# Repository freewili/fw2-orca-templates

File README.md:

# fw2-orca-templates

Example project templates for the FreeWili 2 ORCA module.

Currently supports:

- [KiCad](./kicad) — schematic/PCB template (`ORCATemplate`)
- [Connector pinouts](./PINOUTS.md) — Free Wili OG and Free Wili 2 20-position and 10-position connector pin tables
- [ORCA_NRF example](./examples/ORCA_NRF) — example ORCA module board carrying an NRF24L01 radio
- [GPIO Joiner example](./examples/gpiojoiner) — a routed KiCad 10 star board for testing a pair of FreeWili 2 / OG devices, with fabrication and assembly files

## KiCad template

The `kicad/` directory contains a starter KiCad 7 project (`ORCATemplate`) for
building ORCA module boards, including a 3D `.step` model and a custom
`EEPROM.pretty` footprint library.

The ORCA module connects via two headers, `CN1` and `CN2`:

> **Note:** `kicad/fp-lib-table` currently references footprint libraries
> (`IDC_10`, `IDC_20`) by absolute path on another machine. Update these
> library paths (or replace them with the project-relative `${KIPRJMOD}`
> style used for `EEPROM`) before relying on the template on a fresh
> checkout.

## ORCA_NRF example

The `examples/ORCA_NRF/` directory contains a complete example ORCA module
project built from the template: an NRF24L01 radio carrier with the `CN1`
(20-pin) and `CN2` (10-pin) headers and the ID EEPROM.

User-provided photograph of the assembled ORCA NRF board.

> **Note:** The symbols and footprints are embedded in the schematic and PCB,
> so the project opens without extra libraries. The 3D model references in
> `ORCA_NRF.kicad_pcb` use absolute paths from another machine and will show
> as missing in the 3D viewer until you repoint them.

## GPIO Joiner example

[GPIO Joiner rev A](./examples/gpiojoiner) provides two opposing FreeWili 2
positions and two opposing OG positions. Connect one device per electrical
side, two devices total. A 24LC02BT ORCA EEPROM connects to shared FW2 I2C1.

The example includes editable KiCad sources, project-local symbols,
footprints and 3D models, top/bottom board images, a schematic PDF, and
[prototype manufacturing files](./examples/gpiojoiner/hardware/gpiojoiner/manufacturing/revA).
The [PCBWay quote-form answers](./examples/gpiojoiner/hardware/gpiojoiner/manufacturing/PCBWAY-QUOTE-ANSWERS.md)
show how to request five fully assembled prototypes.

This is an unbuilt prototype: physical mating, EEPROM ID programming and
bench operation remain to be validated. Optional R5-R8 models appear in the
preview but are DNP in the assembly BOM. See the example README for operating
limits and verification evidence.

Repository agent workflow is documented in [AGENTS.md](./AGENTS.md).

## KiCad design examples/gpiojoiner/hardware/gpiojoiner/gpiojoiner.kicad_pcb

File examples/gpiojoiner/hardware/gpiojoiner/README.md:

# GPIO Joiner - rev A review prototype

Open **gpiojoiner.kicad_pro** in KiCad 10 or newer. The schematic, PCB,
symbol library, footprints, and 3D models are included in this folder.
See [schematic PDF](previews/schematic.pdf), [board preview](previews/pcb-top.png),
[design details](DESIGN.md), and [BOM](BOM.md).

[Prototype manufacturing package and order settings](manufacturing/revA/README.md)
are prepared for JLCPCB and PCBWay, including Gerbers, exact-part BOMs,
supplier placement CSVs, and a 1:1 fit/assembly PDF. The working quantity is
five fully assembled boards. No supplier order or live quote has been submitted.

| Top view | Bottom view |
| --- | --- |
|  |  |

These are CAD previews; full device enclosures and physical mating are not
verified. Optional R5-R8 models appear in the views but are DNP in the
prototype assembly BOM.

This revision implements the test cable described in the root
`gpiojoiner spec.md`. It has four docking positions in a star, intended
for **two attached devices: one on Side A and one on Side B**.

```text
                         OG A - J5
                            |
 FW2 A - J1 + J2 -------- JOINER -------- J3 + J4 - FW2 B
                            |
                         OG B - J6
```

| Test pair | Side A | Side B | SW1 position |
| --- | --- | --- | --- |
| FW2 / FW2 | West: J1 and J2 | East: J3 and J4 | FW2 / MIXED |
| OG / OG | North: J5 | South: J6 | OG / OG |
| FW2 / OG | West: J1 and J2 | South: J6 | FW2 / MIXED |
| OG / FW2 | North: J5 | East: J3 and J4 | FW2 / MIXED |

The two connector choices on a side share signals. Four simultaneously
attached devices, or two attached to the same side, are unsupported.
Supporting four attached devices would require added switching or isolation.

## Setup and tests

1. With both devices off, connect one device per side and set SW1.
2. In FW2 / MIXED mode, configure exactly one FW2 to supply VREF; the other
   device uses that external reference. In OG / OG mode, SW1 connects each
   OG's VREF to its own 3.3 V output. Change the switch with power off.
3. Power both devices before driving the shared interfaces. Configure GPIO
   directions and use one SPI clock/chip-select driver. UART/SPI data,
   UART flow control, and GPIO26/27 are crossed as specified.
4. For FW2 / FW2 analog tests, read AOUT0/1 on the other device's AIN0/1.
   Read programmable VOUT as **2 x the opposite AIN2 reading**. Two 10k/10k
   dividers accommodate the published 5.5 V programmable-output maximum.
   AIN3 and GPIO25 have labeled test pads only.

CAN connects only the two FW2 ports; OG SWD pins are unconnected. R7/R8 CAN
termination and R5/R6 I2C1 pull-ups are **DNP**. Check the devices' existing
termination and pull-ups before populating these optional resistors.

## ORCA identification

One **24LC02BT-E/OT** is permanently connected to the shared I2C1 bus on
both FW2 10-pin connectors (pin 7 SCL, pin 9 SDA). Its WP pin is grounded
for programming. A BAT54C diode OR powers it from either FW2's 3.3 V output
without directly joining those supply outputs.

Use a 3.3 V I2C1 bus, up to 400 kHz, with verified pull-ups. I2C1 voltage is
independent of the selected GPIO VREF. Reserve addresses **0x50 through
0x57**: this EEPROM ignores the three low address bits. Coordinate the two
hosts so only one controller accesses the bus at a time unless their
multi-controller behavior has been verified. The diode OR does not isolate
shared signal pins from an unpowered host.

The EEPROM hardware is included; a product-specific ORCA identification
image and a verified programming/boot procedure are still needed. No
identification contents or working auto-detection are claimed by this project.

## Physical and bench validation

The PCB is a 130 x 130 mm cross, two layers, 1.6 mm thick, with four 3.2 mm
mounting holes. FW2 20/10 connector centers are 26.72 mm apart, matching the
named starter template. The original example differs by 0.03 mm. Connector
centers are 3 mm inside the mating board edges. The included connector
models come from the template assembly; full device enclosures were not
available for clearance verification.

Before ordering the prototype, verify actual mating orientation, connector
gender/keying, spacing, board-to-case clearance, and support with real FW2
and OG devices. Check both SW1 contact states on the purchased part. The
project-local switch footprint corrects the installed library's reversed
second-row numbering using the manufacturer contact diagram.

Bench validation must also cover EEPROM supply voltage/read/write and
identification, both VREF modes, power sequencing, I2C pull-ups/ownership,
CAN termination, analog input loading/settling and divider calibration,
and the required test firmware for all four permitted pairs. Manufacturing
inputs are available for prototype quotation and engineering review; hardware
operation remains unverified and this is not a production release.

## Rechecking or regenerating

The editable KiCad files are the delivered design. For a full recheck,
run `tools/verify_project.py` with KiCad's bundled Python; it refreshes the
netlist, ERC/DRC, audits, and verification report. Alternatively, run the standard Python
`tools/check_connections.py` against a freshly exported KiCad XML netlist,
and run `tools/check_pcb.py` with KiCad's bundled Python (`pcbnew`). Also
run KiCad ERC and DRC with schematic parity enabled. Final reports belong
in `reports/`.

`generate_schematic.py` and `generate_pcb.py --rebuild` recreate the CAD
sources and **overwrite manual edits**. The PCB generator requires the
referenced template checkout and installed KiCad libraries. Rebuilding
removes routing. `route_pcb.py --java <java25> --jar <freerouting.jar>`
routes a board with no existing tracks and fills its ground pours.
`finish_routing.py` applies the local edge/thermal and label edits for the
delivered rev A routing; it is specific to those coordinates. A new router
run can produce different geometry and needs a fresh review and finishing
edits. Final KiCad DRC remains required. These development tools are optional for
opening and editing the delivered project.

Library origins and the source revision are recorded in [PROVENANCE.md](PROVENANCE.md).

Optional regeneration tools default to the Windows KiCad 10 install path.
Set `KICAD_INSTALL` for a different installation, and `KICAD_SYMBOL_DIR` when
the symbols are in a separate location. Verification accepts `--cli` for
the KiCad CLI path and needs Python with `pcbnew`. Opening the delivered
project does not require these development scripts or a template checkout.

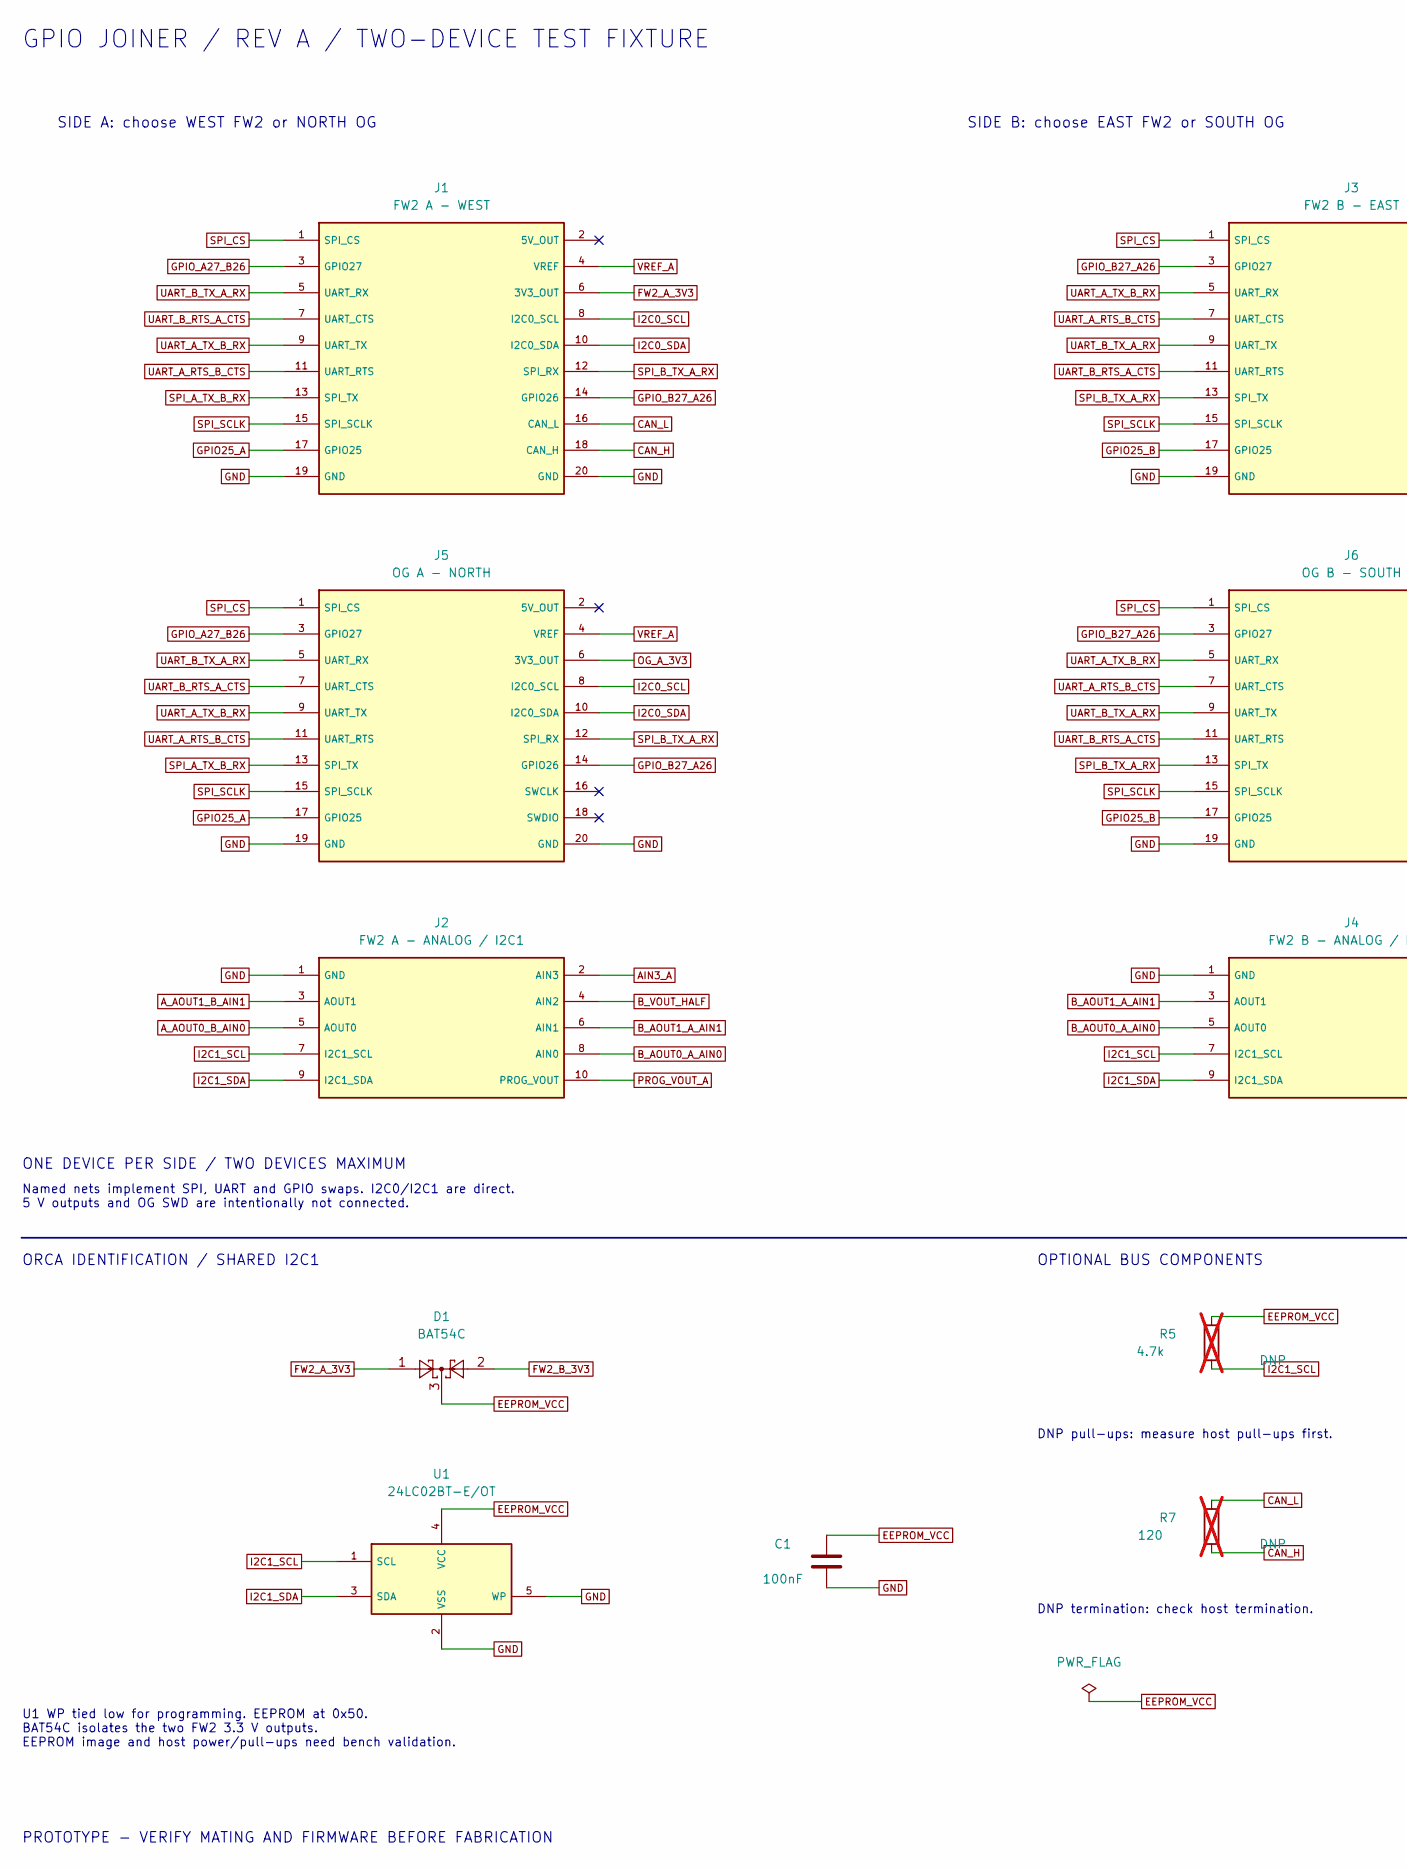
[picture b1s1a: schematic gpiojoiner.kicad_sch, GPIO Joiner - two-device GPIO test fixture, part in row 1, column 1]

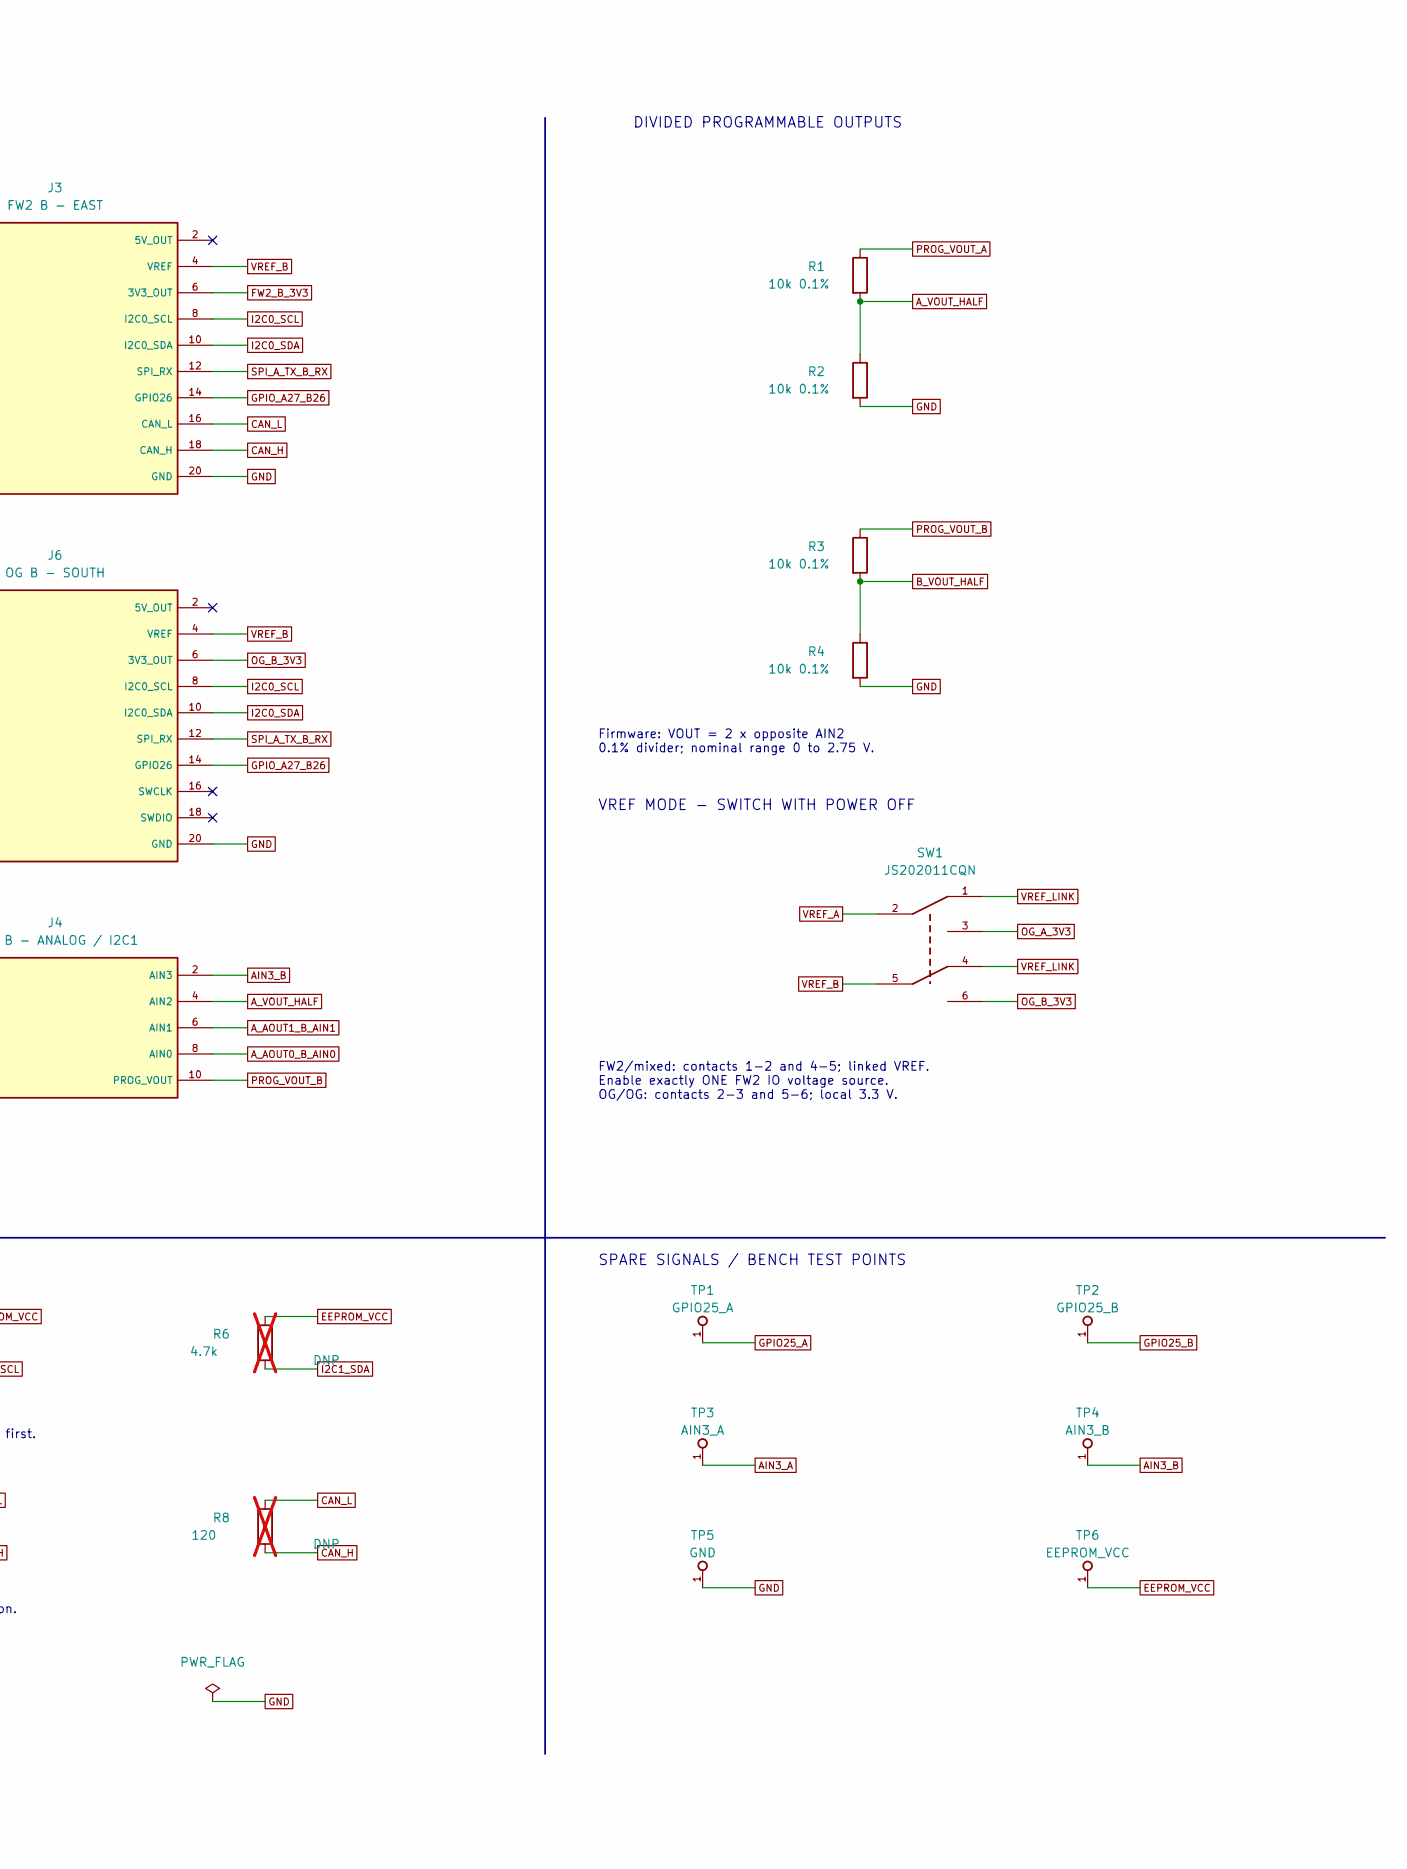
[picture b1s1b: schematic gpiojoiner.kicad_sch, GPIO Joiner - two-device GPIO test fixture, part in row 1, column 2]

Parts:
C1: 100nF; C_0603_1608Metric
D1: BAT54C; SOT-23
J1: FW2 A - WEST; ORCA_20_RA
J2: FW2 A - ANALOG / I2C1; ORCA_10_RA
J3: FW2 B - EAST; ORCA_20_RA
J4: FW2 B - ANALOG / I2C1; ORCA_10_RA
J5: OG A - NORTH; ORCA_20_RA
J6: OG B - SOUTH; ORCA_20_RA
R1, R2, R3, R4: 10k 0.1%; R_0603_1608Metric
R5, R6: 4.7k; R_0603_1608Metric; not fitted
R7, R8: 120; R_0603_1608Metric; not fitted
SW1: JS202011CQN; SW_JS202011CQN
TP1: GPIO25_A; TestPoint_Pad_D1.5mm
TP2: GPIO25_B; TestPoint_Pad_D1.5mm
TP3: AIN3_A; TestPoint_Pad_D1.5mm
TP4: AIN3_B; TestPoint_Pad_D1.5mm
TP5: GND; TestPoint_Pad_D1.5mm
TP6: EEPROM_VCC; TestPoint_Pad_D1.5mm
U1: 24LC02BT-E/OT; SOT-23-5

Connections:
AIN3_A: J2.2 (AIN3), TP3.1
AIN3_B: J4.2 (AIN3), TP4.1
A_AOUT0_B_AIN0: J2.5 (AOUT0), J4.8 (AIN0)
A_AOUT1_B_AIN1: J2.3 (AOUT1), J4.6 (AIN1)
A_VOUT_HALF: J4.4 (AIN2), R1.2, R2.1
B_AOUT0_A_AIN0: J2.8 (AIN0), J4.5 (AOUT0)
B_AOUT1_A_AIN1: J2.6 (AIN1), J4.3 (AOUT1)
B_VOUT_HALF: J2.4 (AIN2), R3.2, R4.1
CAN_H: J1.18 (CAN_H), J3.18 (CAN_H), R7.2, R8.2
CAN_L: J1.16 (CAN_L), J3.16 (CAN_L), R7.1, R8.1
EEPROM_VCC: C1.1, D1.3, R5.1, R6.1, TP6.1, U1.4 (VCC)
FW2_A_3V3: D1.1, J1.6 (3V3_OUT)
FW2_B_3V3: D1.2, J3.6 (3V3_OUT)
GND: C1.2, J1.19 (GND), J1.20 (GND), J2.1 (GND), J3.19 (GND), J3.20 (GND), J4.1 (GND), J5.19 (GND), J5.20 (GND), J6.19 (GND), J6.20 (GND), R2.2, R4.2, TP5.1, U1.2 (VSS), U1.5 (WP)
GPIO25_A: J1.17 (GPIO25), J5.17 (GPIO25), TP1.1
GPIO25_B: J3.17 (GPIO25), J6.17 (GPIO25), TP2.1
GPIO_A27_B26: J1.3 (GPIO27), J3.14 (GPIO26), J5.3 (GPIO27), J6.14 (GPIO26)
GPIO_B27_A26: J1.14 (GPIO26), J3.3 (GPIO27), J5.14 (GPIO26), J6.3 (GPIO27)
I2C0_SCL: J1.8 (I2C0_SCL), J3.8 (I2C0_SCL), J5.8 (I2C0_SCL), J6.8 (I2C0_SCL)
I2C0_SDA: J1.10 (I2C0_SDA), J3.10 (I2C0_SDA), J5.10 (I2C0_SDA), J6.10 (I2C0_SDA)
I2C1_SCL: J2.7 (I2C1_SCL), J4.7 (I2C1_SCL), R5.2, U1.1 (SCL)
I2C1_SDA: J2.9 (I2C1_SDA), J4.9 (I2C1_SDA), R6.2, U1.3 (SDA)
OG_A_3V3: J5.6 (3V3_OUT), SW1.3
OG_B_3V3: J6.6 (3V3_OUT), SW1.6
PROG_VOUT_A: J2.10 (PROG_VOUT), R1.1
PROG_VOUT_B: J4.10 (PROG_VOUT), R3.1
SPI_A_TX_B_RX: J1.13 (SPI_TX), J3.12 (SPI_RX), J5.13 (SPI_TX), J6.12 (SPI_RX)
SPI_B_TX_A_RX: J1.12 (SPI_RX), J3.13 (SPI_TX), J5.12 (SPI_RX), J6.13 (SPI_TX)
SPI_CS: J1.1 (SPI_CS), J3.1 (SPI_CS), J5.1 (SPI_CS), J6.1 (SPI_CS)
SPI_SCLK: J1.15 (SPI_SCLK), J3.15 (SPI_SCLK), J5.15 (SPI_SCLK), J6.15 (SPI_SCLK)
UART_A_RTS_B_CTS: J1.11 (UART_RTS), J3.7 (UART_CTS), J5.11 (UART_RTS), J6.7 (UART_CTS)
UART_A_TX_B_RX: J1.9 (UART_TX), J3.5 (UART_RX), J5.9 (UART_TX), J6.5 (UART_RX)
UART_B_RTS_A_CTS: J1.7 (UART_CTS), J3.11 (UART_RTS), J5.7 (UART_CTS), J6.11 (UART_RTS)
UART_B_TX_A_RX: J1.5 (UART_RX), J3.9 (UART_TX), J5.5 (UART_RX), J6.9 (UART_TX)
VREF_A: J1.4 (VREF), J5.4 (VREF), SW1.2
VREF_B: J3.4 (VREF), J6.4 (VREF), SW1.5
VREF_LINK: SW1.1, SW1.4

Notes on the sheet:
GPIO JOINER / REV A / TWO-DEVICE TEST FIXTURE
SIDE A: choose WEST FW2 or NORTH OG
SIDE B: choose EAST FW2 or SOUTH OG
DIVIDED PROGRAMMABLE OUTPUTS
Firmware: VOUT = 2 x opposite AIN2 0.1% divider; nominal range 0 to 2.75 V.
ONE DEVICE PER SIDE / TWO DEVICES MAXIMUM
Named nets implement SPI, UART and GPIO swaps. I2C0/I2C1 are direct. 5 V outputs and OG SWD are intentionally not connected.
ORCA IDENTIFICATION / SHARED I2C1
OPTIONAL BUS COMPONENTS
DNP pull-ups: measure host pull-ups first.
DNP termination: check host termination.
VREF MODE - SWITCH WITH POWER OFF
FW2/mixed: contacts 1-2 and 4-5; linked VREF. Enable exactly ONE FW2 IO voltage source. OG/OG: contacts 2-3 and 5-6; local 3.3 V.
SPARE SIGNALS / BENCH TEST POINTS
U1 WP tied low for programming. EEPROM at 0x50. BAT54C isolates the two FW2 3.3 V outputs. EEPROM image and host power/pull-ups need bench validation.
PROTOTYPE - VERIFY MATING AND FIRMWARE BEFORE FABRICATION

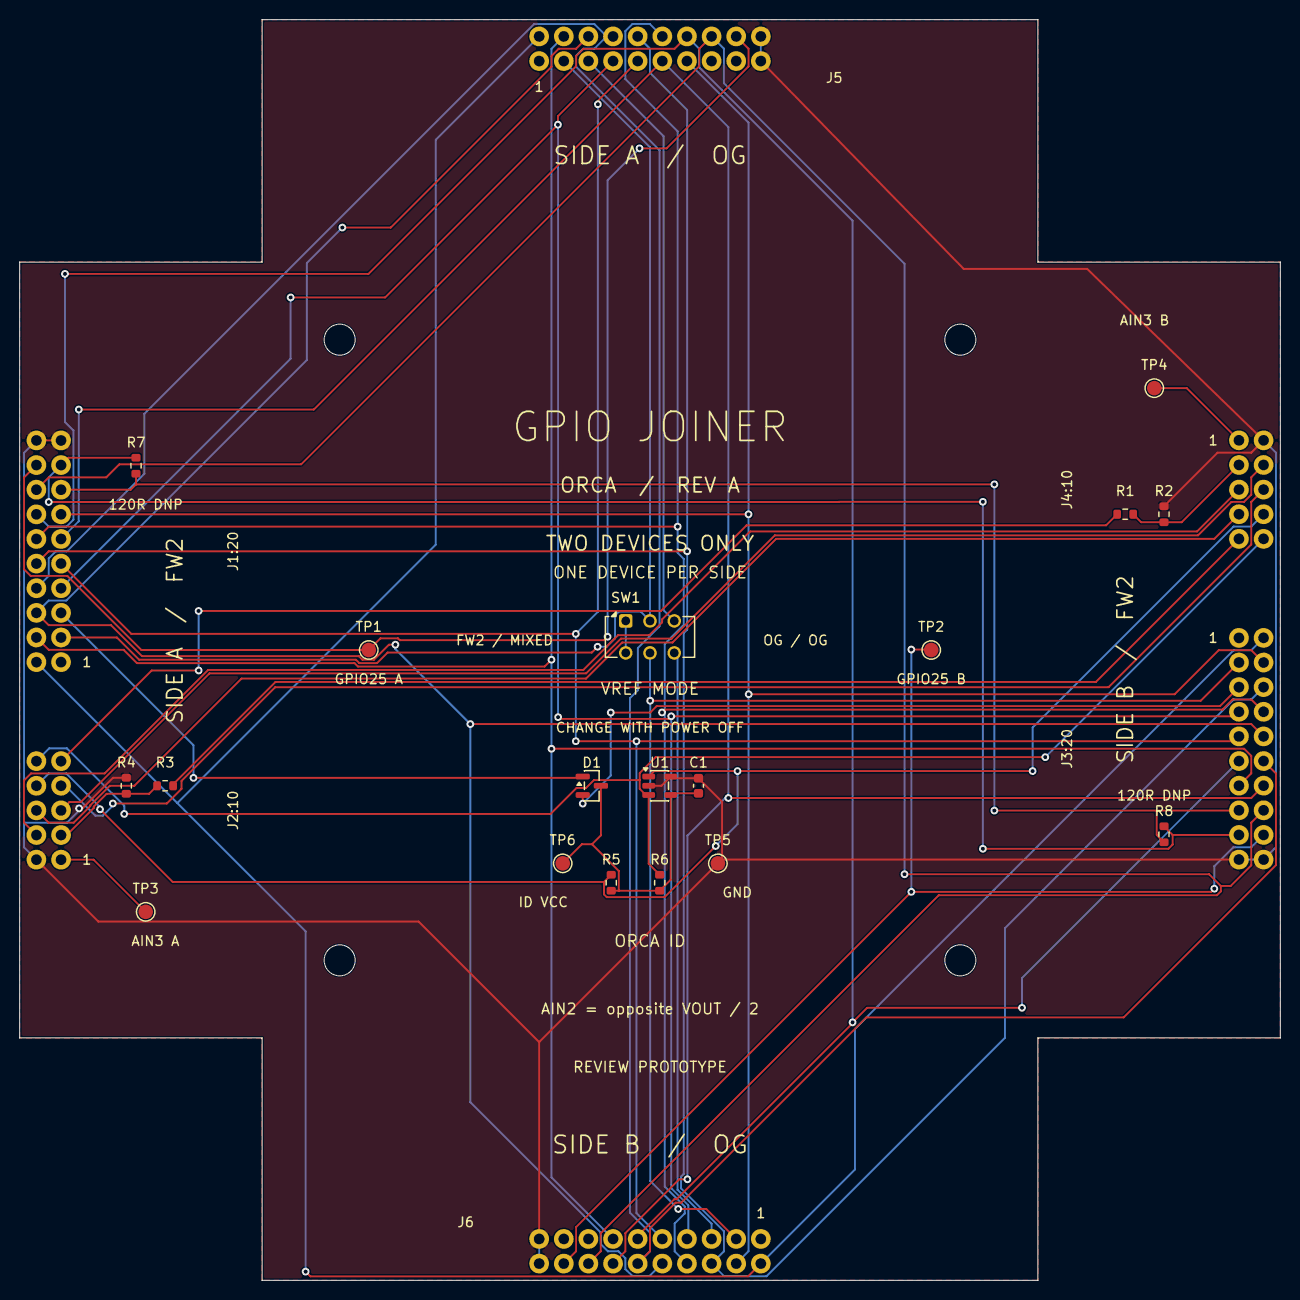
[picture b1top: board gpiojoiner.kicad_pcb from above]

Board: 2 copper layers, 130.0 x 130.0 mm, 28 parts (0 on the bottom side), 37 nets.

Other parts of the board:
H1, H2, H3, H4: MountingHole_3.2mm_M3

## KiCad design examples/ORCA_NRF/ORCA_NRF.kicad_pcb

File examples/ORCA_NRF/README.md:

# ORCA NRF example

NRF radio carrier example for FreeWili 2.

Open [ORCA_NRF.kicad_pro](ORCA_NRF.kicad_pro) in KiCad to inspect the
[schematic](ORCA_NRF.kicad_sch) and [PCB](ORCA_NRF.kicad_pcb).

The photograph shows the assembled example board. The existing PCB's 3D
model references include absolute paths; see the [repository notes](../../README.md#orca_nrf-example)
when opening its 3D view on another machine.

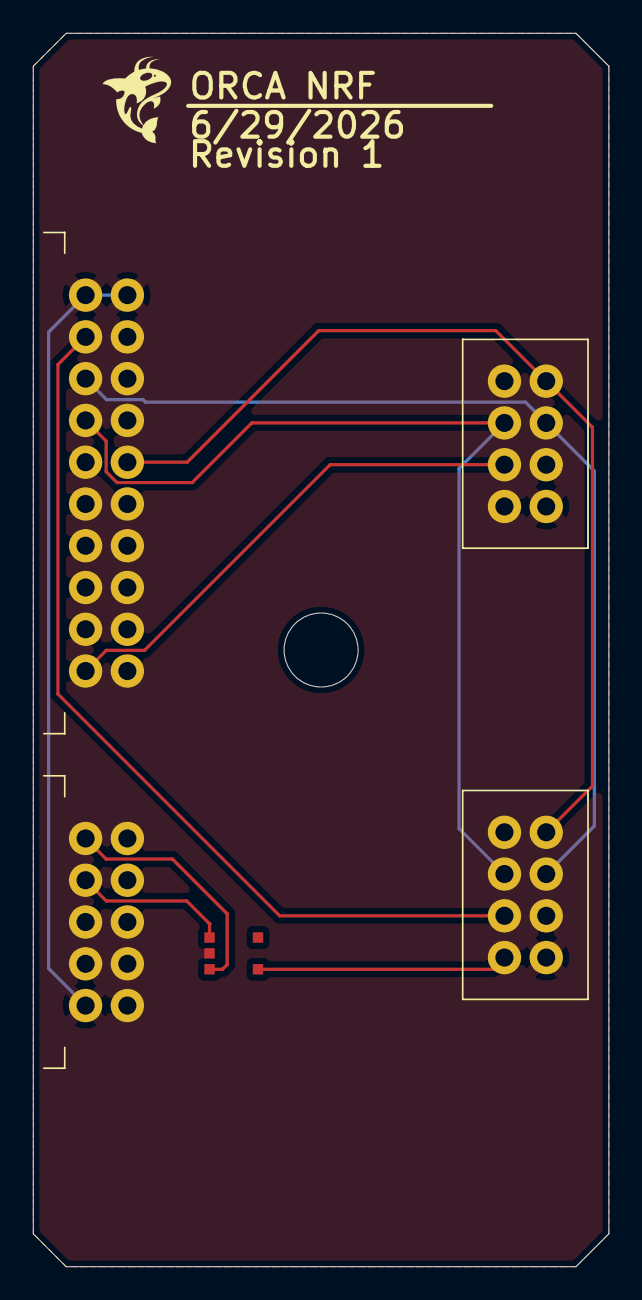
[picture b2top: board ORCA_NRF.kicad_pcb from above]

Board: 2 copper layers, 35.0 x 75.0 mm, 5 parts (0 on the bottom side), 9 nets.

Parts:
CN1: IDC_20_Print
CN2: IDC_10_Print
CN3, CN4: NRF_F_CN
EEPROM1: 24LC02BT-E_OT

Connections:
3V3: CN1.6 (3V3), CN3.2 (VCC), CN4.2 (VCC), EEPROM1.4 (VCC)
GND: CN1.19 (GND), CN1.20 (GND), CN2.1 (GND), CN3.1 (GND), CN4.1 (GND), EEPROM1.2 (VSS)
unnamed: CN1.17 (GPIO25), CN4.4 (CSN)
unnamed: CN1.12 (SPI1_Rx), CN3.7 (MISO), CN4.7 (MISO)
unnamed: CN1.15 (SPI1_SCLK), CN3.5 (SCK), CN4.5 (SCK)
unnamed: CN1.13 (SPI1_Tx), CN3.6 (MOSI), CN4.6 (MOSI)
unnamed: CN1.1 (SPI_CS), CN3.4 (CSN)
unnamed: CN2.7 (SCLM1), EEPROM1.1 (SCL)
unnamed: CN2.9 (SDAM1), EEPROM1.3 (SDA)
